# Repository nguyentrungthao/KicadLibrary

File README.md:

# KicadLibrary
symbol and footprints for kicad

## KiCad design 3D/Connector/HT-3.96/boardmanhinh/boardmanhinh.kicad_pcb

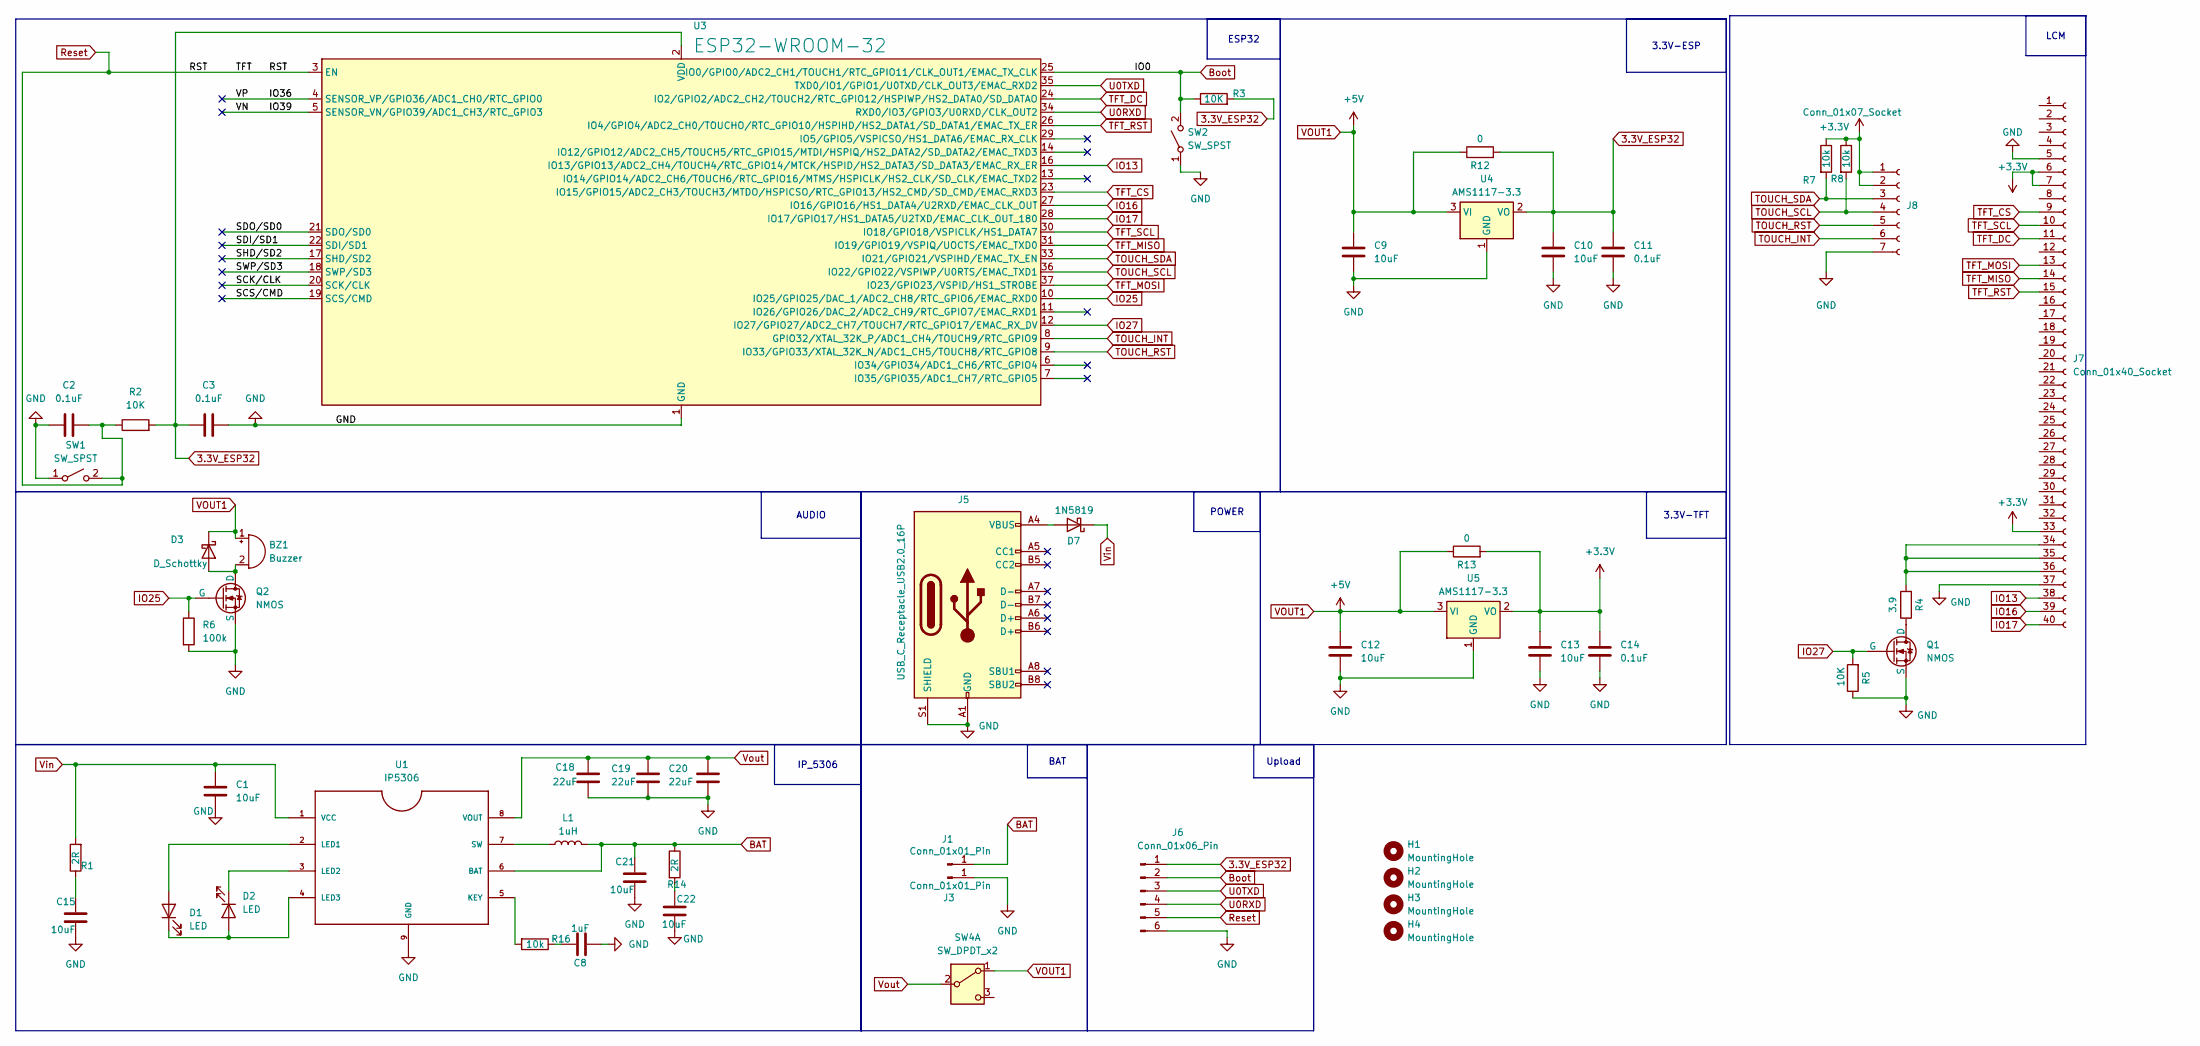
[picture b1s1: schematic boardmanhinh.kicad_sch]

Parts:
BZ1: Buzzer; 9056-TS DIP Buzzer
C1, C9, C10, C12, C13, C15, C21, C22: 10uF; C_0603_1608Metric
C2, C3, C11, C14: 0.1uF; C_0603_1608Metric
C8: 1uF; C_0603_1608Metric
C18, C19, C20: 22uF; C_0805_2012Metric
D1, D2: LED; LED_0603_1608Metric
D3: D_Schottky; D_SMA
D7: 1N5819; D_0603_1608Metric
H1, H2, H3, H4: MountingHole; MountingHole_2.2mm_M2_ISO7380_Pad
J1, J3: Conn_01x01_Pin; TestPoint_Keystone_5019_Minature
J5: USB_C_Receptacle_USB2.0_16P; USB_C_Receptacle_GCT_USB4105-xx-A_16P_TopMnt_Horizontal
J6: Conn_01x06_Pin; PinHeader_1x06_P2.54mm_Vertical
J7: Conn_01x40_Socket; TE_4-1734839-0_1x40-1MP_P0.5mm_Horizontal
J8: Conn_01x07_Socket; TE_0-1734839-7_1x07-1MP_P0.5mm_Horizontal
L1: 1uH; L_Cenker_CKCS4020
Q1, Q2: NMOS; SOT-23
R1, R14: 2R; R_0603_1608Metric
R2, R3, R5: 10K; R_0603_1608Metric
R4: 3.9; R_0603_1608Metric
R6: 100k; R_0603_1608Metric
R7, R8, R16: 10k; R_0603_1608Metric
R12, R13: 0; R_0603_1608Metric
SW1, SW2: SW_SPST; SW_SPST_PTS810
SW4: SW_DPDT_x2; SW_Slide-03_Wuerth-WS-SLTV_10x2.5x6.4_P2.54mm
U1: IP5306; SOIC9P127_490X600X170L84X42T330X241N
U3: ESP32-WROOM-32; ESP32-WROOM-32E
U4, U5: AMS1117-3.3; SOT-223-3_TabPin2

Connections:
3.3V_ESP32: C3.1, C10.2, C11.2, J6.1, R2.2, R3.2, R12.2, U3.2 (VDD), U4.2 (VO)
+3.3V: C13.2, C14.2, J7.6, J7.7, J7.33, J8.1, J8.2, R7.1, R8.1, R13.2, U5.2 (VO)
/IO36: U3.4 (SENSOR_VP/GPIO36/ADC1_CH0/RTC_GPIO0)
/IO39: U3.5 (SENSOR_VN/GPIO39/ADC1_CH3/RTC_GPIO3)
/SCK/CLK: U3.20 (SCK/CLK)
/SCS/CMD: U3.19 (SCS/CMD)
/SDI/SD1: U3.22 (SDI/SD1)
/SDO/SD0: U3.21 (SDO/SD0)
/SHD/SD2: U3.17 (SHD/SD2)
/SWP/SD3: U3.18 (SWP/SD3)
BAT: C21.1, J1.1, L1.2, R14.1, U1.6 (BAT); also elsewhere on the board
Boot: J6.2, R3.1, SW2.2 (B), U3.25 (IO0/GPIO0/ADC2_CH1/TOUCH1/RTC_GPIO11/CL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); also elsewhere on the board
GND: C1.2, C2.1, C3.2, C8.1, C9.1, C10.1, C11.1, C12.1, C13.1, C14.1, C15.2, C18.2, C19.2, C20.2, C21.2, C22.2, J3.1, J5.A1 (GND), J5.A12 (GND), J5.B1 (GND), J5.B12 (GND), J5.S1 (SHIELD), J6.6, J7.5, J7.37, J8.7, Q1.2 (S), Q2.2 (S), R5.1, R6.2, SW1.1 (A), SW2.1 (A), U1.9 (GND), U3.1 (GND), U3.15 (GND), U3.38 (GND), U3.39 (GND), U4.1 (GND), U5.1 (GND); also elsewhere on the board
IO13: J7.38, U3.16 (IO13/GPIO13/ADC2_CH4/TOUCH4/RTC_GPIO14/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)
IO16: J7.39, U3.27 (IO16/GPIO16/HS1_DATA4/U2RXD/EMAC_CLK_OUT)
IO17: J7.40, U3.28 (IO17/GPIO17/HS1_DATA5/U2TXD/EMAC_CLK_OU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)
IO25: Q2.1 (G), R6.1, U3.10 (IO25/GPIO25/DAC_1/ADC2_CH8/RTC_GPIO6/EM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)
IO27: Q1.1 (G), R5.2, U3.12 (IO27/GPIO27/ADC2_CH7/TOUCH7/RTC_GPIO17/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)
unnamed: BZ1.2 (-), D3.2 (A), Q2.3 (D)
unnamed: C8.2, R16.1
unnamed: C15.1, R1.1
unnamed: C22.1, R14.2
unnamed: D1.2 (A), U1.2 (LED1)
unnamed: D1.1 (K), D2.2 (A), U1.4 (LED3)
unnamed: D2.1 (K), U1.3 (LED2)
unnamed: D7.2 (A), J5.A4 (VBUS), J5.A9 (VBUS), J5.B4 (VBUS), J5.B9 (VBUS)
unnamed: J7.34, J7.35, J7.36, R4.2
unnamed: Q1.3 (D), R4.1
unnamed: R16.2, U1.5 (KEY)
unnamed: L1.1, U1.7 (SW)
Reset: C2.2, J6.5, R2.1, SW1.2 (B), U3.3 (EN); also elsewhere on the board
TFT_CS: J7.9, U3.23 (IO15/GPIO15/ADC2_CH3/TOUCH3/MTDO/HSPICS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)
TFT_DC: J7.11, U3.24 (IO2/GPIO2/ADC2_CH2/TOUCH2/RTC_GPIO12/HS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)
TFT_MISO: J7.14, U3.31 (IO19/GPIO19/VSPIQ/UOCTS/EMAC_TXD0)
TFT_MOSI: J7.13, U3.37 (IO23/GPIO23/VSPID/HS1_STROBE)
TFT_RST: J7.15, U3.26 (IO4/GPIO4/ADC2_CH0/TOUCHO/RTC_GPIO10/HS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)
TFT_SCL: J7.10, U3.30 (IO18/GPIO18/VSPICLK/HS1_DATA7)
TOUCH_INT: J8.6, U3.8 (GPIO32/XTAL_32K_P/ADC1_CH4/TOUCH9/RTC_G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)
TOUCH_RST: J8.5, U3.9 (IO33/GPIO33/XTAL_32K_N/ADC1_CH5/TOUCH8/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)
TOUCH_SCL: J8.4, R8.2, U3.36 (IO22/GPIO22/VSPIWP/U0RTS/EMAC_TXD1)
TOUCH_SDA: J8.3, R7.2, U3.33 (IO21/GPIO21/VSPIHD/EMAC_TX_EN)
U0RXD: J6.4, U3.34 (RXD0/IO3/GPIO3/U0RXD/CLK_OUT2)
U0TXD: J6.3, U3.35 (TXD0/IO1/GPIO1/U0TXD/CLK_OUT3/EMAC_RXD2)
VOUT1: BZ1.1 (+), C9.2, C12.2, D3.1 (K), R12.1, R13.1, SW4.1 (A), U4.3 (VI), U5.3 (VI)
Vin: C1.1, D7.1 (K), R1.2, U1.1 (VCC)
Vout: C18.1, C19.1, C20.1, SW4.2 (B), U1.8 (VOUT)

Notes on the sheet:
Upload
3.3V-TFT
ESP32
LCM
AUDIO
3.3V-ESP
IP_5306
POWER
BAT

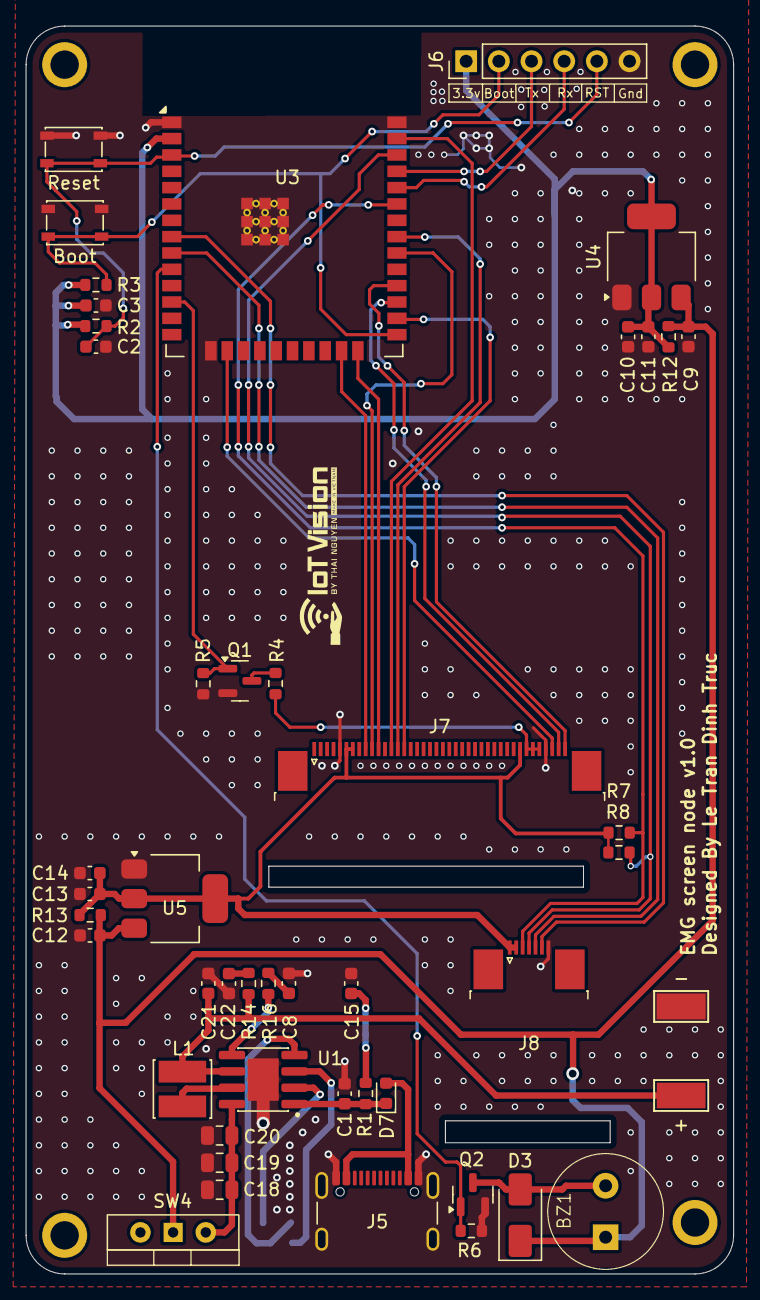
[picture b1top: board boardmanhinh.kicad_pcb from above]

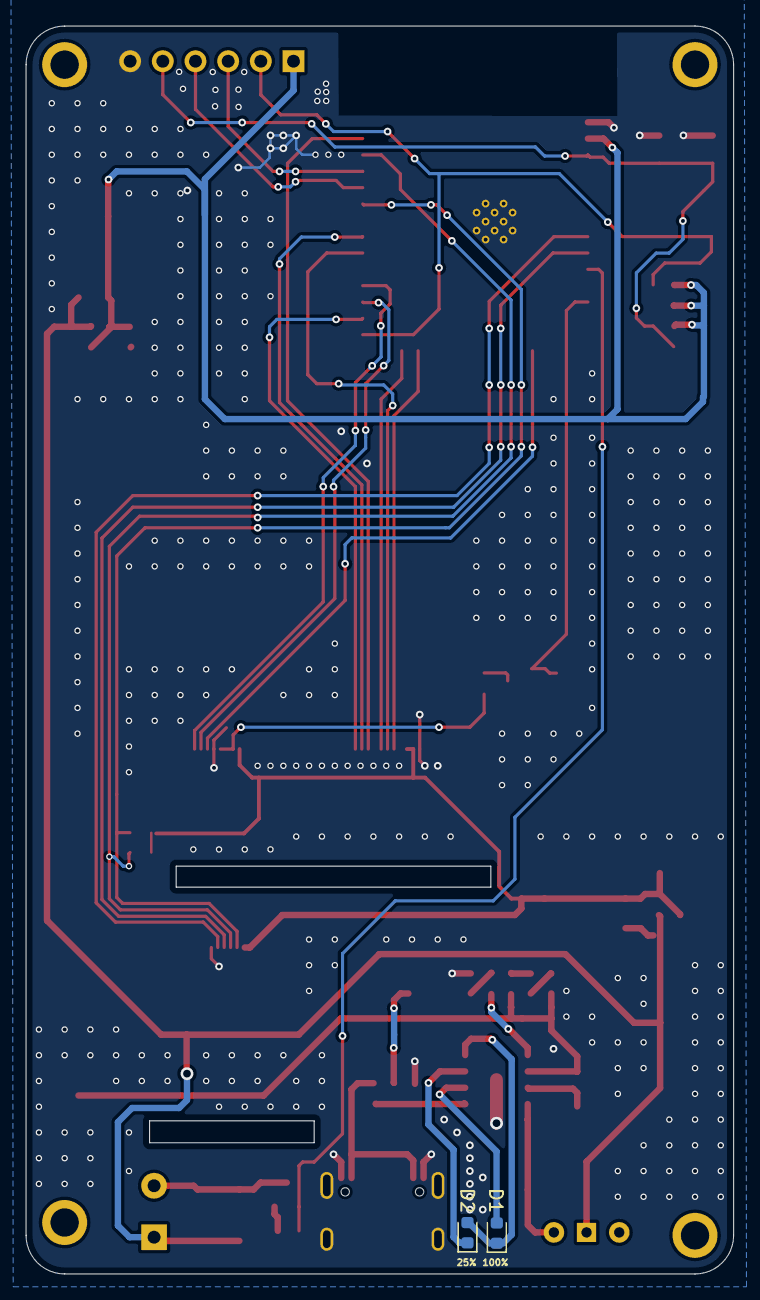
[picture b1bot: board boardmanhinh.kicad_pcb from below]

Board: 2 copper layers, 55.0 x 97.0 mm, 53 parts (2 on the bottom side), 38 nets.

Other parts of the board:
+: Conn_01x01_Pin; TestPoint_Keystone_5019_Minature
-: Conn_01x01_Pin; TestPoint_Keystone_5019_Minature
Boot: SW_SPST; SW_SPST_PTS810
Reset: SW_SPST; SW_SPST_PTS810

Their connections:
BAT: +.1; also elsewhere on the board
Boot: Boot.2 (B); also elsewhere on the board
GND: -.1, Boot.1 (A), Reset.1 (A); also elsewhere on the board
Reset: Reset.2 (B); also elsewhere on the board

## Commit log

2024-09-17 Synchronize
2024-09-17 update 3D
